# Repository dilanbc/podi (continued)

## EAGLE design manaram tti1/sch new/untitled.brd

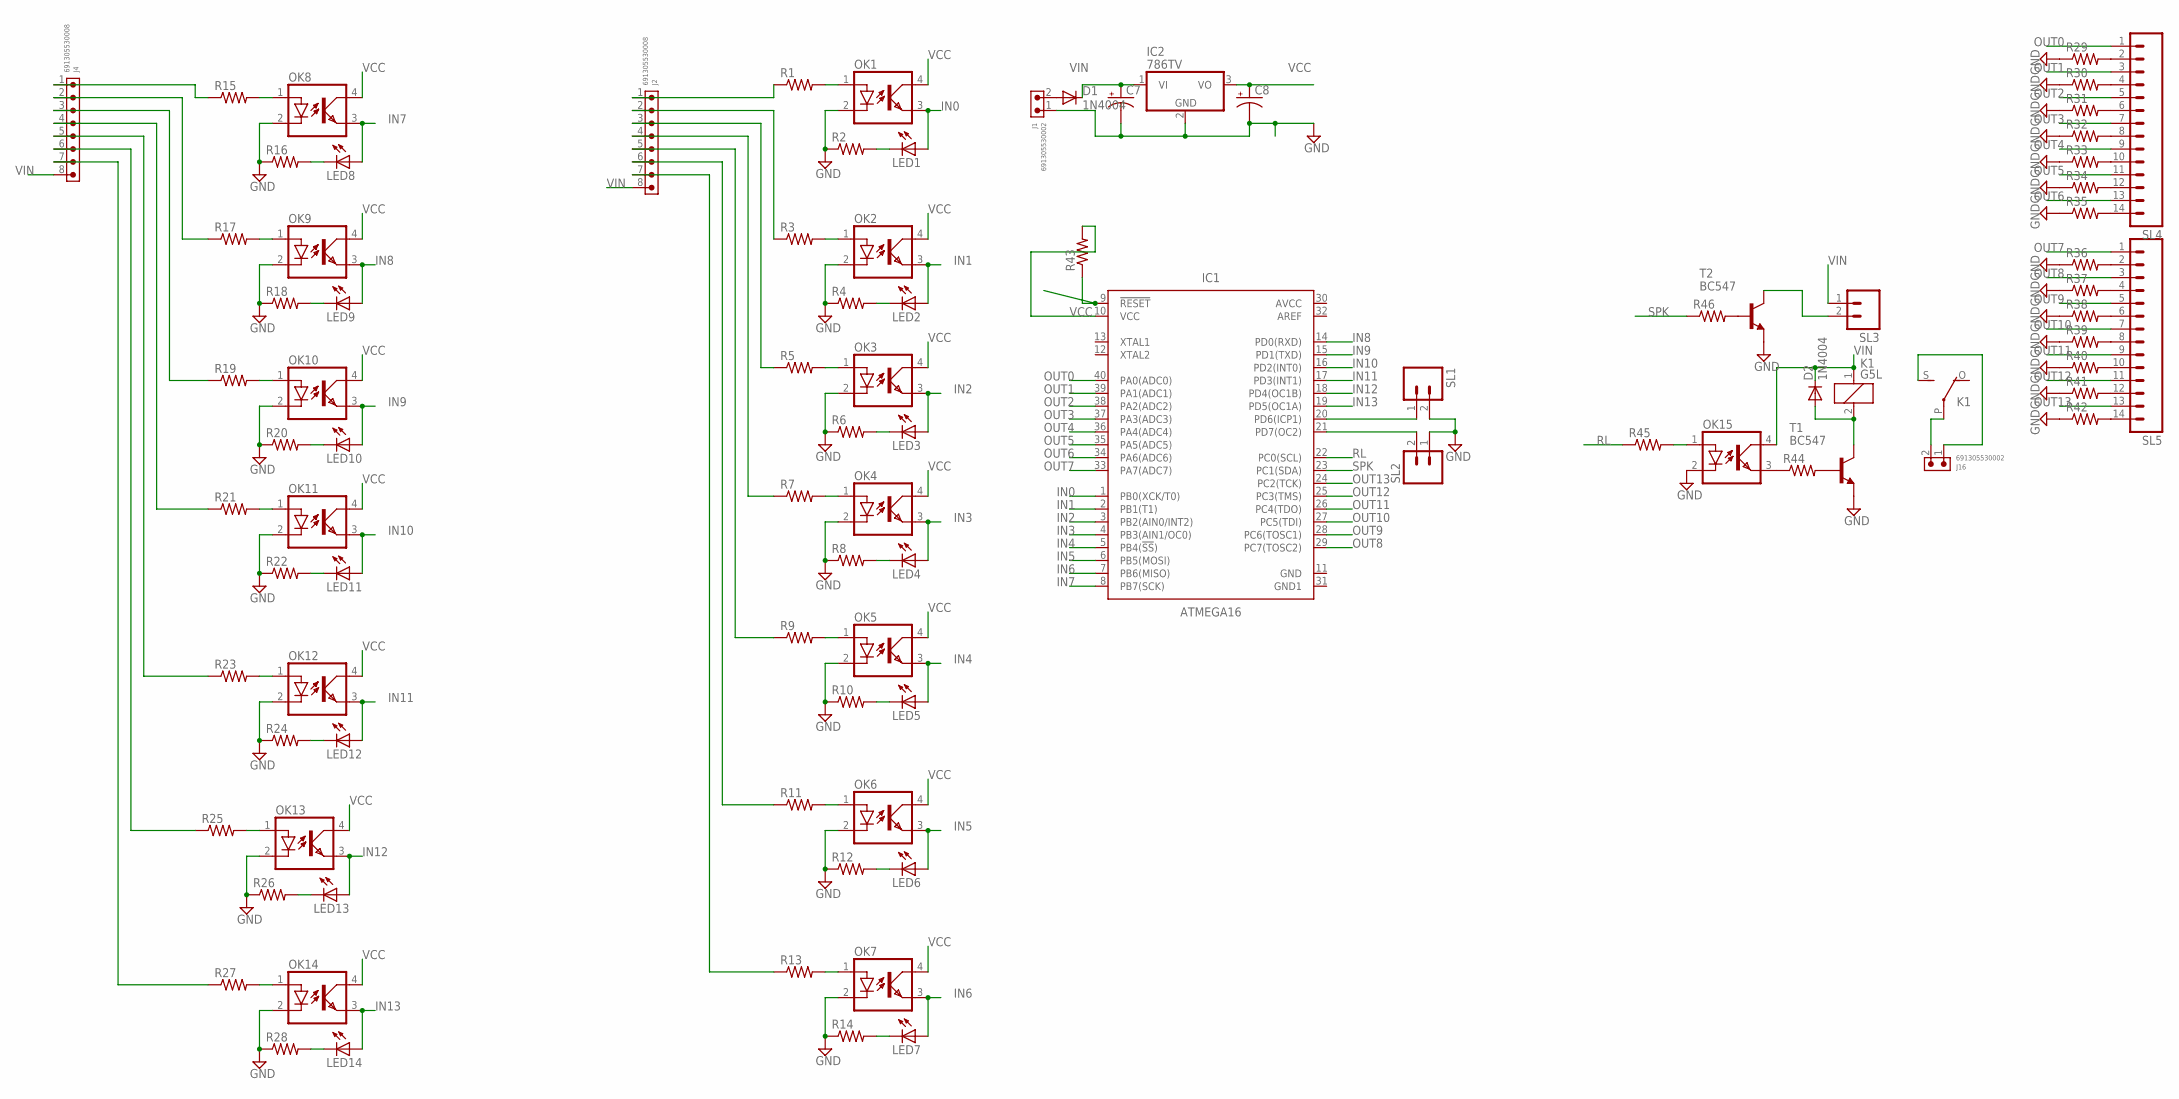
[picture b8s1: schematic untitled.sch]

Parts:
C7: CAPACITOR-PE5-10.5; E5-10,5
C8: CAPACITOR-PE5-6; E5-6
D1, D2: 1N4004; DO41-10
IC1: ATMEGA16; DIP1587W56P254L5229H482Q40B
IC2: 786TV; TO220V
J1, J16: 691305530002
J2, J4: 691305530008
K1: G5L; G5LE
LED1, LED2, LED3, LED4, LED5, LED6, LED7, LED8, LED9, LED10, LED11, LED12, LED13, LED14: LED3MM
OK1, OK2, OK3, OK4, OK5, OK6, OK7, OK8, OK9, OK10, OK11, OK12, OK13, OK14, OK15: PC817; DIL04
R1, R3, R5, R7, R9, R11, R13, R15, R17, R19, R21, R23, R25, R27, R45: R-US_0204/2V; 0204V
R2, R4, R6, R8, R10, R12, R14, R16, R18, R20, R22, R24, R26, R28, R29, R30, R31, R32, R33, R34, R35, R36, R37, R38, R39, R40, R41, R42, R43, R44, R46: R-US_0207/7; 0207/7
SL1, SL2, SL3: M02; 02P
SL4, SL5: M14; 14P
T1, T2: BC547; TO92

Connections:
AVCC: IC1.30 (AVCC)
GND: C7.-, C8.-, IC1.11 (GND), IC2.2 (GND), J1.1, OK1.2 (C), OK2.2 (C), OK3.2 (C), OK4.2 (C), OK5.2 (C), OK6.2 (C), OK7.2 (C), OK8.2 (C), OK9.2 (C), OK10.2 (C), OK11.2 (C), OK12.2 (C), OK13.2 (C), OK14.2 (C), OK15.2 (C), R2.1, R4.1, R6.1, R8.1, R10.1, R12.1, R14.1, R16.1, R18.1, R20.1, R22.1, R24.1, R26.1, R28.1, R29.1, R30.1, R31.1, R32.1, R33.1, R34.1, R35.1, R36.1, R37.1, R38.1, R39.1, R40.1, R41.1, R42.1, SL1.2, SL2.1, T1.1 (E), T2.1 (E)
GND1: IC1.31 (GND1)
IN0: IC1.1 (PB0(XCK/T0)), LED1.A, OK1.3 (EMIT)
IN1: IC1.2 (PB1(T1)), LED2.A, OK2.3 (EMIT)
IN2: IC1.3 (PB2(AIN0/INT2)), LED3.A, OK3.3 (EMIT)
IN3: IC1.4 (PB3(AIN1/OC0)), LED4.A, OK4.3 (EMIT)
IN4: IC1.5 (PB4(!SS!)), LED5.A, OK5.3 (EMIT)
IN5: IC1.6 (PB5(MOSI)), LED6.A, OK6.3 (EMIT)
IN6: IC1.7 (PB6(MISO)), LED7.A, OK7.3 (EMIT)
IN7: IC1.8 (PB7(SCK)), LED8.A, OK8.3 (EMIT)
IN8: IC1.14 (PD0(RXD)), LED9.A, OK9.3 (EMIT)
IN9: IC1.15 (PD1(TXD)), LED10.A, OK10.3 (EMIT)
IN10: IC1.16 (PD2(INT0)), LED11.A, OK11.3 (EMIT)
IN11: IC1.17 (PD3(INT1)), LED12.A, OK12.3 (EMIT)
IN12: IC1.18 (PD4(OC1B)), LED13.A, OK13.3 (EMIT)
IN13: IC1.19 (PD5(OC1A)), LED14.A, OK14.3 (EMIT)
unnamed: J2.1, R1.1
unnamed: J2.2, R3.1
unnamed: OK1.1 (A), R1.2
unnamed: J2.3, R5.1
unnamed: IC1.9 (!RESET!), R43.1
unnamed: LED1.K (C), R2.2
unnamed: J2.4, R7.1
unnamed: OK2.1 (A), R3.2
unnamed: J2.5, R9.1
unnamed: R29.2, SL4.2
unnamed: LED2.K (C), R4.2
unnamed: J2.6, R11.1
unnamed: OK3.1 (A), R5.2
unnamed: R30.2, SL4.4
unnamed: R31.2, SL4.6
unnamed: LED3.K (C), R6.2
unnamed: J4.2, R17.1
unnamed: OK4.1 (A), R7.2
unnamed: R32.2, SL4.8
unnamed: R33.2, SL4.10
unnamed: LED4.K (C), R8.2
unnamed: J4.4, R21.1
unnamed: OK5.1 (A), R9.2
unnamed: R34.2, SL4.12
unnamed: R35.2, SL4.14
unnamed: LED5.K (C), R10.2
unnamed: J4.6, R25.1
unnamed: OK6.1 (A), R11.2
unnamed: R36.2, SL5.2
unnamed: R37.2, SL5.4
unnamed: LED6.K (C), R12.2
unnamed: J2.7, R13.1
unnamed: OK7.1 (A), R13.2
unnamed: R38.2, SL5.6
unnamed: R39.2, SL5.8
unnamed: LED7.K (C), R14.2
unnamed: J4.1, R15.1
unnamed: OK8.1 (A), R15.2
unnamed: R40.2, SL5.10
unnamed: R41.2, SL5.12
unnamed: LED8.K (C), R16.2
unnamed: R42.2, SL5.14
unnamed: OK9.1 (A), R17.2
unnamed: D2.A, K1.2, T1.3 (C)
unnamed: R44.2, T1.2 (B)
unnamed: LED9.K (C), R18.2
unnamed: J4.3, R19.1
unnamed: OK10.1 (A), R19.2
unnamed: OK15.3 (EMIT), R44.1
unnamed: OK15.1 (A), R45.2
unnamed: LED10.K (C), R20.2
unnamed: D1.A, J1.2
unnamed: OK11.1 (A), R21.2
unnamed: SL3.2, T2.3 (C)
unnamed: R46.2, T2.2 (B)
unnamed: LED11.K (C), R22.2
unnamed: J4.5, R23.1
unnamed: OK12.1 (A), R23.2
unnamed: LED12.K (C), R24.2
unnamed: OK13.1 (A), R25.2
unnamed: LED13.K (C), R26.2
unnamed: J4.7, R27.1
unnamed: OK14.1 (A), R27.2
unnamed: LED14.K (C), R28.2
unnamed: IC1.20 (PD6(ICP1)), SL1.1
unnamed: IC1.21 (PD7(OC2)), SL2.2
unnamed: J16.2, K1.P
unnamed: J16.1, K1.S
OUT0: IC1.40 (PA0(ADC0)), SL4.1
OUT1: IC1.39 (PA1(ADC1)), SL4.3
OUT2: IC1.38 (PA2(ADC2)), SL4.5
OUT3: IC1.37 (PA3(ADC3)), SL4.7
OUT4: IC1.36 (PA4(ADC4)), SL4.9
OUT5: IC1.35 (PA5(ADC5)), SL4.11
OUT6: IC1.34 (PA6(ADC6)), SL4.13
OUT7: IC1.33 (PA7(ADC7)), SL5.1
OUT8: IC1.29 (PC7(TOSC2)), SL5.3
OUT9: IC1.28 (PC6(TOSC1)), SL5.5
OUT10: IC1.27 (PC5(TDI)), SL5.7
OUT11: IC1.26 (PC4(TDO)), SL5.9
OUT12: IC1.25 (PC3(TMS)), SL5.11
OUT13: IC1.24 (PC2(TCK)), SL5.13
RL: IC1.22 (PC0(SCL)), R45.1
SPK: IC1.23 (PC1(SDA)), R46.1
VCC: C8.+, IC1.10 (VCC), IC2.3 (VO), OK1.4 (COL), OK2.4 (COL), OK3.4 (COL), OK4.4 (COL), OK5.4 (COL), OK6.4 (COL), OK7.4 (COL), OK8.4 (COL), OK9.4 (COL), OK10.4 (COL), OK11.4 (COL), OK12.4 (COL), OK13.4 (COL), OK14.4 (COL), R43.2
VIN: C7.+, D1.C, D2.C, IC2.1 (VI), J2.8, J4.8, K1.1, OK15.4 (COL), SL3.1

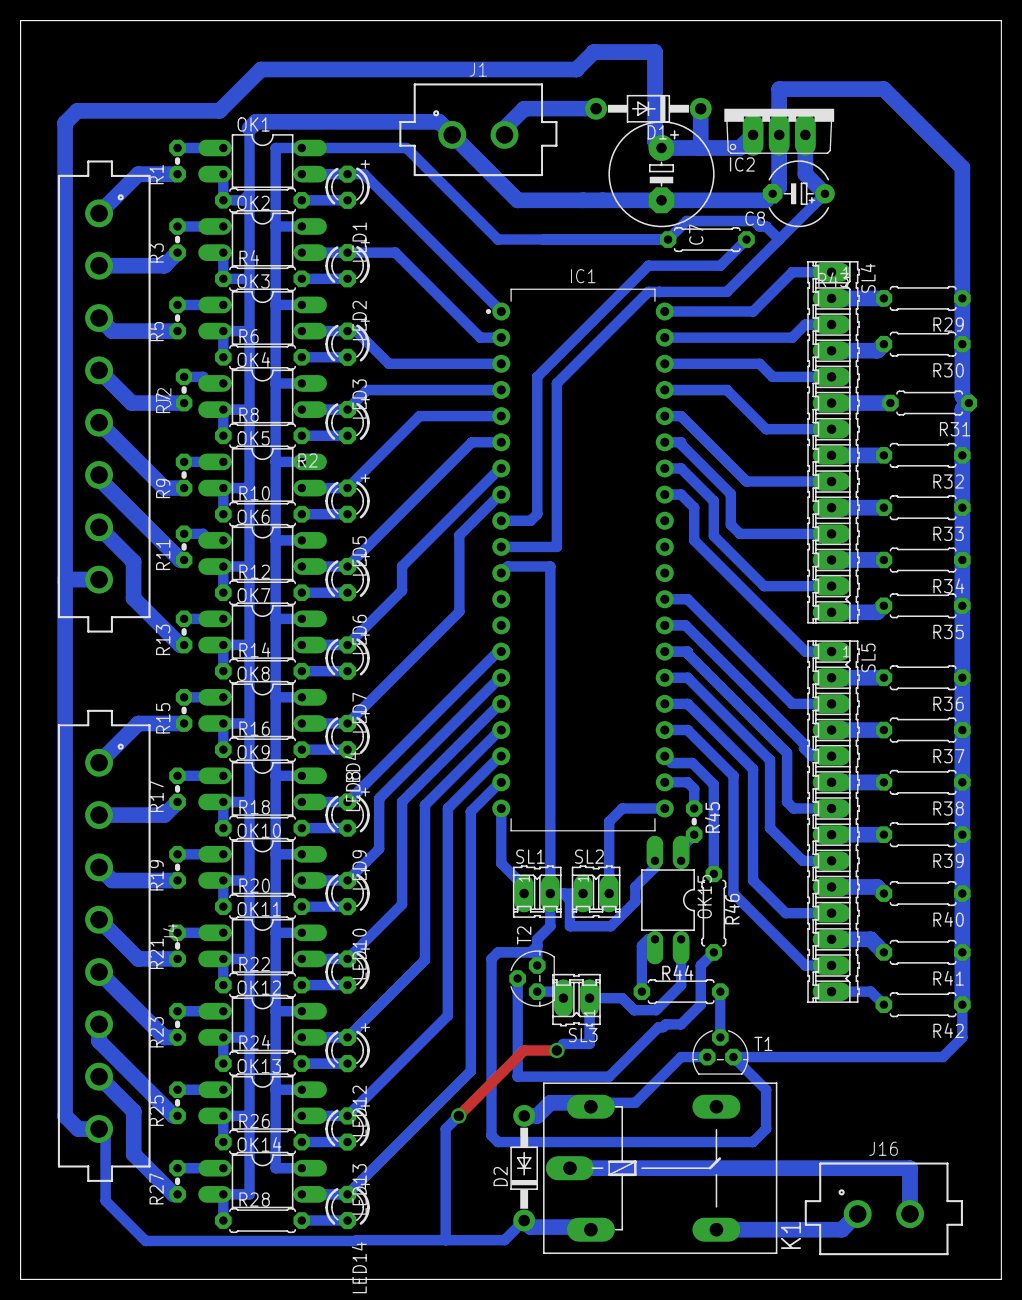
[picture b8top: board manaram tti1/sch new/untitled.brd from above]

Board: 2 copper layers, 95.2 x 122.2 mm, 93 parts (0 on the bottom side), 101 nets.

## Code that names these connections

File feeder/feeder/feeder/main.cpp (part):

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	//1- joy x
	//2-joy y
	//3-potentiol
	//pd0 main push button
}
uint16_t ReadADC(uint8_t ADCchannel)
{
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
void xaxisInit(){
	
	/*PD2 and PD3*/
	DDRD&=~(1<<2);
	DDRD&=~(1<<3);
	
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

void yaxisInit(){
	/*PB1 and PB2*/
	DDRB&=~(1<<1);
	DDRB&=~(1<<2);
	
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void axisControlInit(){
	 DDRD |= (1 << 6);
	 DDRD |= (1 << 5);
	 // PD6 and PD5 is now an output

	 OCR0A = 0;
	 OCR0B=0;
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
